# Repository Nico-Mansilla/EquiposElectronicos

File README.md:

# Poyecto para la asignatura de diseño de equipos electrónicos

Este proyecto consistió en diseñar una PCB tipo "expansion board" para la tarjeta STM32 nucleo, con el objetivo de conectar un motor DC con encoder y un potenciómetro para controlar su posición como servo motor.

El diseño fue realizado en Eagle y se encuentra en la carpeta con ese nombre, consiste en una placa simple de dos capas y con el tamaño necesario para que sus pines se conecten directamente con los pines d el atarjeta nucleo, se envió a PCBway para su fabricación.

Se compraron los componentes SMD por Mouser y se soldaron a la PCB con un horno.

Finalmente de diseñó la lógica en STM32 IDE con un controlador PI y la medición del encoder para controlar la posición del motor DC.

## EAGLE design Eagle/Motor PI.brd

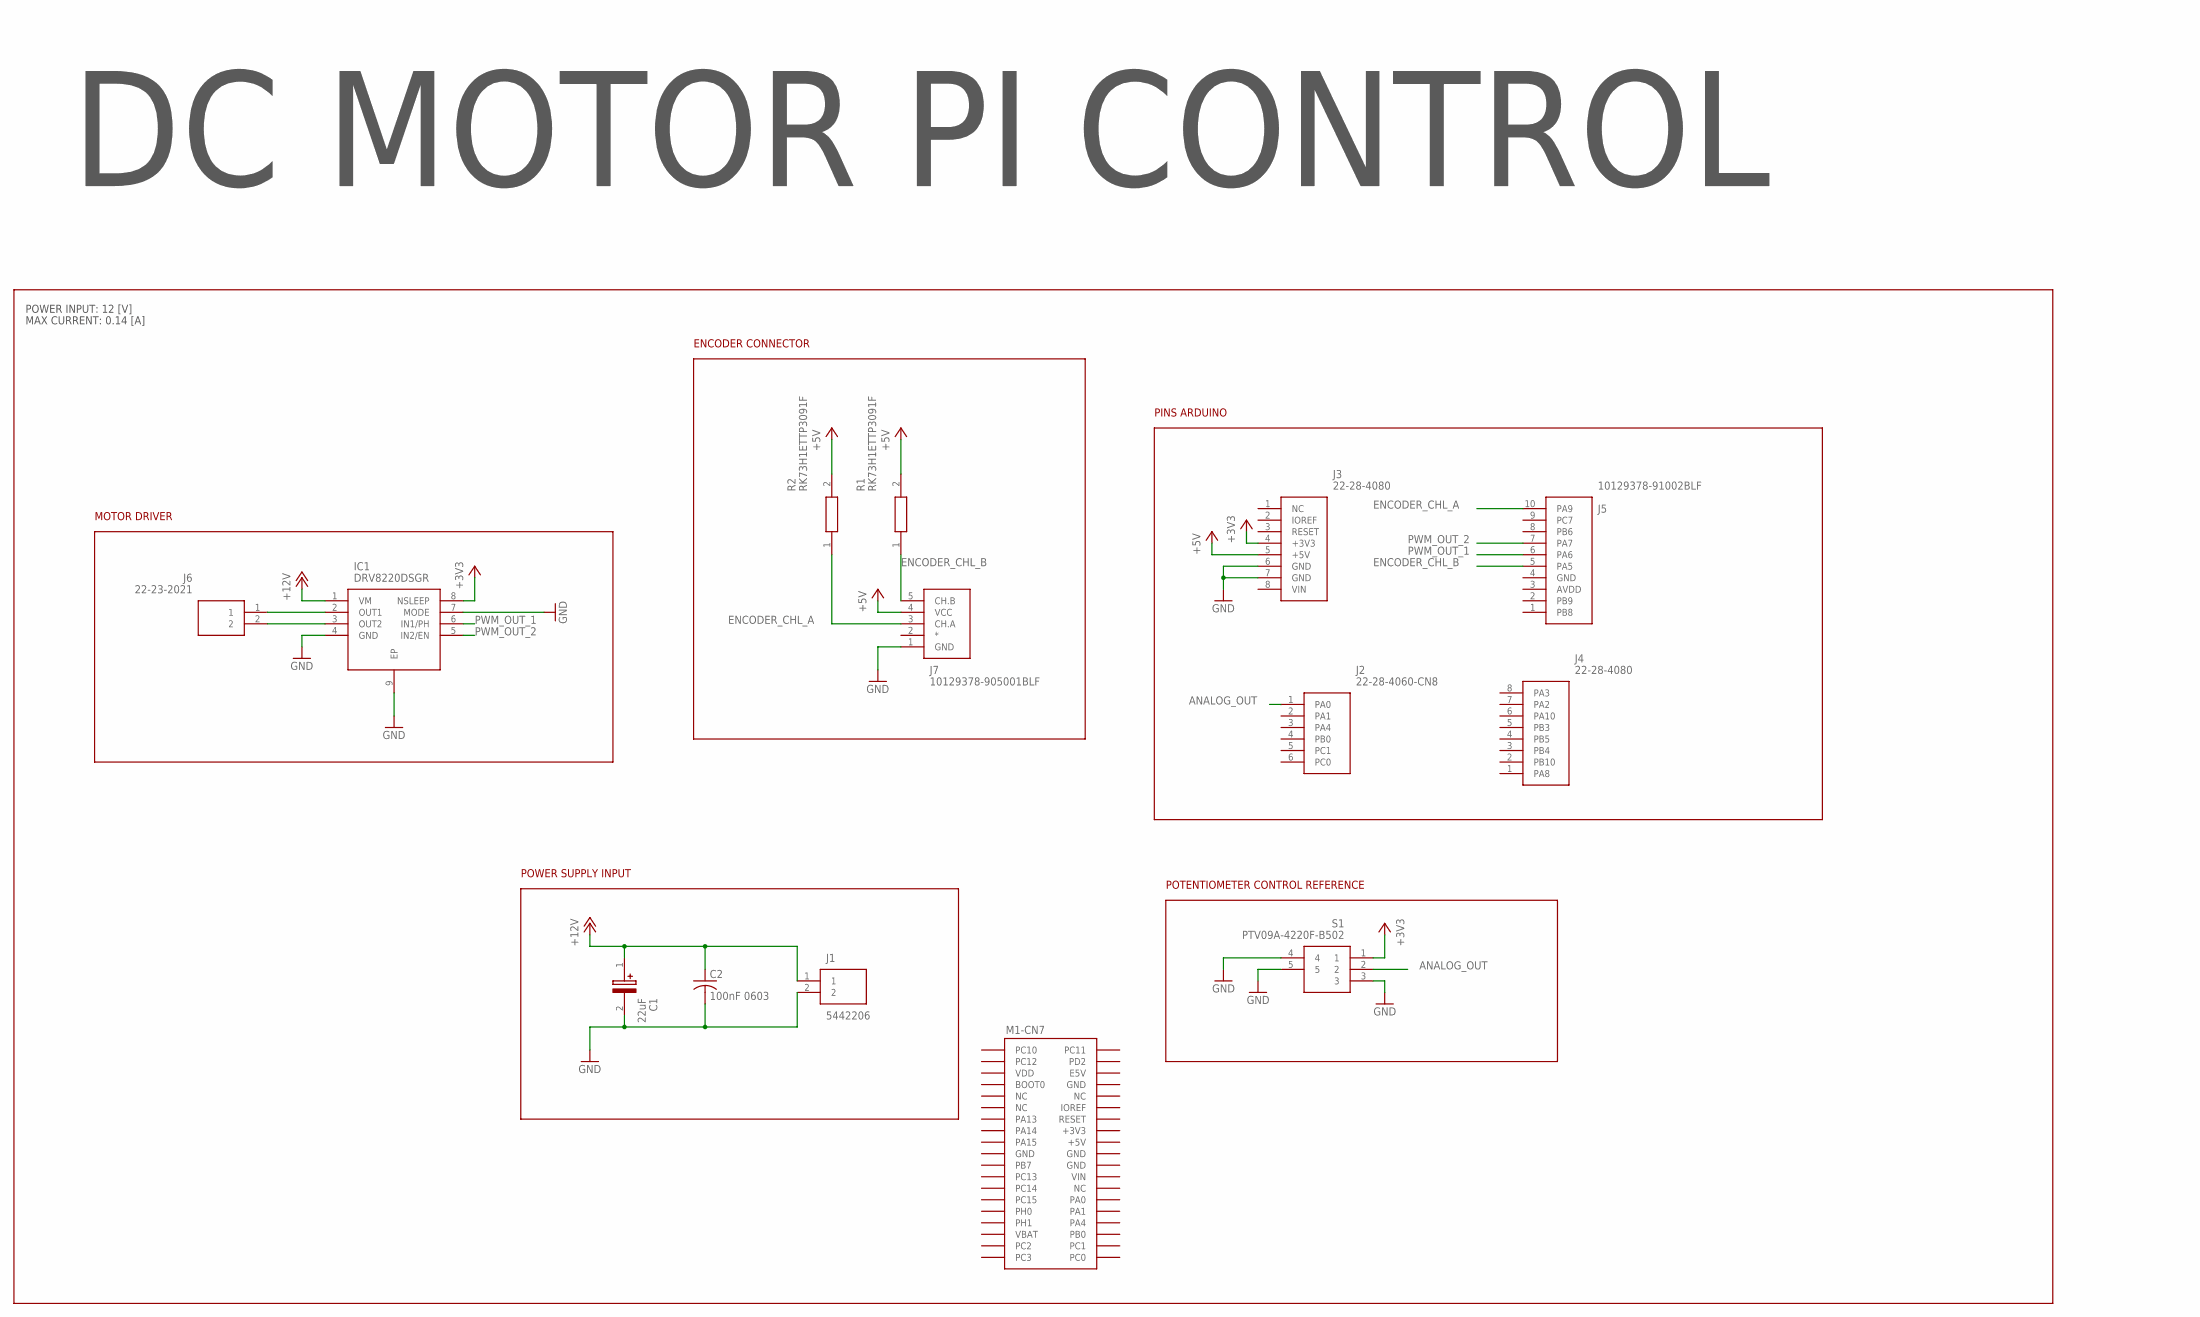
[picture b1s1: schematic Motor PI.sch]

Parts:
C1: 22uF; CAPPRD200W52D500H1250; PARTNO 860020472004
C2: 100nF 0603; C0603
IC1: DRV8220DSGR; SON50P200X200X80-9N; PARTNO DRV8220DSGR
J1: 5442206; PARTNO 5442206
J2: 22-28-4060-CN8; HDRV6W66P0X254_1X6_1524X249X83-CN8; PARTNO 22-28-4060
J3: 22-28-4080; HDRV6W66P0X254_1X6_1524X249X83
J4: 22-28-4080; HDRV6W66P0X254_1X6_1524X249X83; PARTNO 22-28-4080
J5: 10129378-91002BLF; HDRV6W66P0X254_1X6_1524X249X83
J6: 22-23-2021; SHDR2W87P0X254_1X2_493X635X110; PARTNO 22-23-2021
J7: 10129378-905001BLF; HDRV6W66P0X254_1X6_1524X249X83; PARTNO 10129378-905001BLF
M1: NUCLEO-L452RE; NUCLEO-64
R1, R2: RK73H1ETTP3091F; RESC1005X40N; PARTNO RK73H1ETTP3091F
S1: PTV09A-4220F-B502; PTV09A4020FB103; PARTNO PTV09A-4220F-B103

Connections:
+3V3: IC1.8 (NSLEEP), J3.4 (+3V3), M1.CN6-4 (+3V3), M1.CN7-16 (+3V3), S1.1
+5V: J3.5 (+5V), J7.4 (VCC), M1.CN6-5 (+5V), M1.CN7-18 (+5V), R1.2, R2.2
+12V: C1.1 (+), C2.1, IC1.1 (VM), J1.1
AGND: M1.CN10-32 (AGND)
ANALOG_OUT: J2.1 (PA0), S1.2
AVDD: M1.CN5-8 (AVDD), M1.CN10-7 (AVDD)
ENCODER_CHL_A: J5.10 (PA9), J7.3 (CH.A), R2.1
ENCODER_CHL_B: J5.5 (PA5), J7.5 (CH.B), R1.1
GND: C1.2 (-), C2.2, IC1.4 (GND), IC1.7 (MODE), IC1.9 (EP), J1.2, J3.6 (GND), J3.7 (GND), J5.4 (GND), J7.1 (GND), M1.CN5-7 (GND), M1.CN6-6 (GND), M1.CN6-7 (GND), M1.CN7-8 (GND), M1.CN7-19 (GND), M1.CN7-20 (GND), M1.CN7-22 (GND), M1.CN10-9 (GND), M1.CN10-20 (GND), S1.3, S1.4, S1.5
IOREF: M1.CN6-2 (IOREF)
unnamed: IC1.2 (OUT1), J6.1
unnamed: IC1.3 (OUT2), J6.2
PWM_OUT_1: IC1.6 (IN1/PH), J5.6 (PA6)
PWM_OUT_2: IC1.5 (IN2/EN), J5.7 (PA7)
U5V: M1.CN10-8 (U5V)
VBAT: M1.CN7-33 (VBAT)
VDD: M1.CN7-5 (VDD)
VIN: M1.CN6-8 (VIN), M1.CN7-24 (VIN)

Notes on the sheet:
PINS ARDUINO
POTENTIOMETER CONTROL REFERENCE
POWER SUPPLY INPUT
MOTOR DRIVER
ENCODER CONNECTOR
DC MOTOR PI CONTROL
POWER INPUT: 12 [V]
MAX CURRENT: 0.14 [A]

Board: 2 copper layers, 14 parts (0 on the bottom side), 13 nets, no tracks yet.

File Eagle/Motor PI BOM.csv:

"Part";"Value";"Device";"Package";"Description";"DESCRIPTION";"HEIGHT";"MANUFACTURER_NAME";"MANUFACTURER_PART_NUMBER";"MOUSER_PART_NUMBER";"MOUSER_PRICE-STOCK";"PARTNO";"POPULARITY";"SPICEPREFIX";"UTMEL_PART_NUMBER";"UTMEL_PRICE-STOCK";
"C1";"22uF";"860020472004";"CAPPRD200W52D500H1250";"Wurth Elektronik 22uF 25 V dc Aluminium Electrolytic Capacitor, WCAP-ATG5 Series 2000h 5 (Dia.) x 11mm";"Wurth Elektronik 22uF 25 V dc Aluminium Electrolytic Capacitor, WCAP-ATG5 Series 2000h 5 (Dia.) x 11mm";"12.5mm";"Wurth Elektronik";"860020472004";"710-860020472004";"https://www.mouser.co.uk/ProductDetail/Wurth-Elektronik/8600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";"860020472004";"";"";"";"";
"C2";"100nF 0603";"C-USC0603";"C0603";"CAPACITOR, American symbol";"";"";"";"";"";"";"";"37";"C";"";"";
"IC1";"DRV8220DSGR";"DRV8220DSGR";"SON50P200X200X80-9N";"DRV8220DSGR";"DRV8220DSGR";"0.8mm";"Texas Instruments";"DRV8220DSGR";"";"";"DRV8220DSGR";"";"";"";"";
"J1";"5442206";"5442206";"5442206";"Fixed Terminal Blocks BC-508X10- 2 GN 5.08 MM PITCH";"Fixed Terminal Blocks BC-508X10- 2 GN 5.08 MM PITCH";"10.15mm";"Phoenix Contact";"5442206";"651-5442206";"https://www.mouser.co.uk/ProductDetail/Phoenix-Contact/54422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";"5442206";"";"";"";"";
"J2";"22-28-4060-CN8";"22-28-4060-CN8";"HDRV6W66P0X254_1X6_1524X249X83-CN8";"MOLEX - 22-28-4060 - CONNECTOR, HEADER, 6POS, 1ROW, 2.54MM";"MOLEX - 22-28-4060 - CONNECTOR, HEADER, 6POS, 1ROW, 2.54MM";"8.38mm";"Molex";"22-28-4060";"538-22-28-4060";"https://www.mouser.co.uk/ProductDetail/Molex/22-28-4060?qs=d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";"22-28-4060";"";"";"";"";
"J3";"22-28-4080";"22-28-4080";"HDRV6W66P0X254_1X6_1524X249X83";"MOLEX - 22-28-4080 - CONNECTOR, HEADER, 8POS, 1ROW, 2.54MM";"";"";"";"";"";"";"";"";"";"";"";
"J4";"22-28-4080";"22-28-4080";"HDRV6W66P0X254_1X6_1524X249X83";"MOLEX - 22-28-4080 - CONNECTOR, HEADER, 8POS, 1ROW, 2.54MM";"";"";"";"";"";"";"22-28-4080";"";"";"";"";
"J5";"10129378-91002BLF";"10129378-91002BLF";"HDRV6W66P0X254_1X6_1524X249X83";"MOLEX - 22-28-4080 - CONNECTOR, HEADER, 8POS, 1ROW, 2.54MM";"";"";"";"";"";"";"";"";"";"";"";
"J6";"22-23-2021";"22-23-2021";"SHDR2W87P0X254_1X2_493X635X110";"Headers & Wire Housings VERT PCB HDR 2P TIN FRICTION LOCK";"Headers & Wire Housings VERT PCB HDR 2P TIN FRICTION LOCK";"11.05mm";"Molex";"22-23-2021";"538-22-23-2021";"https://www.mouser.co.uk/ProductDetail/Molex/22-23-2021?qs=I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";"22-23-2021";"";"";"";"";
"J7";"10129378-905001BLF";"10129378-905001BLF";"HDRV6W66P0X254_1X6_1524X249X83";"10129378-905001BLF";"";"";"";"";"";"";"10129378-905001BLF";"";"";"";"";
"R1";"RK73H1ETTP3091F";"RK73H1ETTP3091F";"RESC1005X40N";"Thick Film Resistors - SMD 0.1watts 3.09Kohms";"Thick Film Resistors - SMD 0.1watts 3.09Kohms";"0.4mm";"KOA Speer";"RK73H1ETTP3091F";"660-RK73H1ETTP3091F";"https://www.mouser.com/Search/Refine.aspx?Keyword=660-RK73H1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";"RK73H1ETTP3091F";"";"";"";"";
"R2";"RK73H1ETTP3091F";"RK73H1ETTP3091F";"RESC1005X40N";"Thick Film Resistors - SMD 0.1watts 3.09Kohms";"Thick Film Resistors - SMD 0.1watts 3.09Kohms";"0.4mm";"KOA Speer";"RK73H1ETTP3091F";"660-RK73H1ETTP3091F";"https://www.mouser.com/Search/Refine.aspx?Keyword=660-RK73H1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";"RK73H1ETTP3091F";"";"";"";"";
"S1";"PTV09A-4220F-B502";"PTV09A-4220F-B502";"PTV09A4020FB103";"Potentiometers 5K LINEAR 20%";"Potentiometers 5K LINEAR 20%";"20mm";"Bourns";"PTV09A-4220F-B502";"652-PTV09A-4220FB502";"https://www.mouser.co.uk/ProductDetail/Bourns/PTV09A-4220F-B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";"PTV09A-4220F-B103";"";"";"";"";

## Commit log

2025-05-20 Added base libraries
2025-05-20 firmware and readme added
2025-05-20 radme corrections
2025-05-20 folder changes
